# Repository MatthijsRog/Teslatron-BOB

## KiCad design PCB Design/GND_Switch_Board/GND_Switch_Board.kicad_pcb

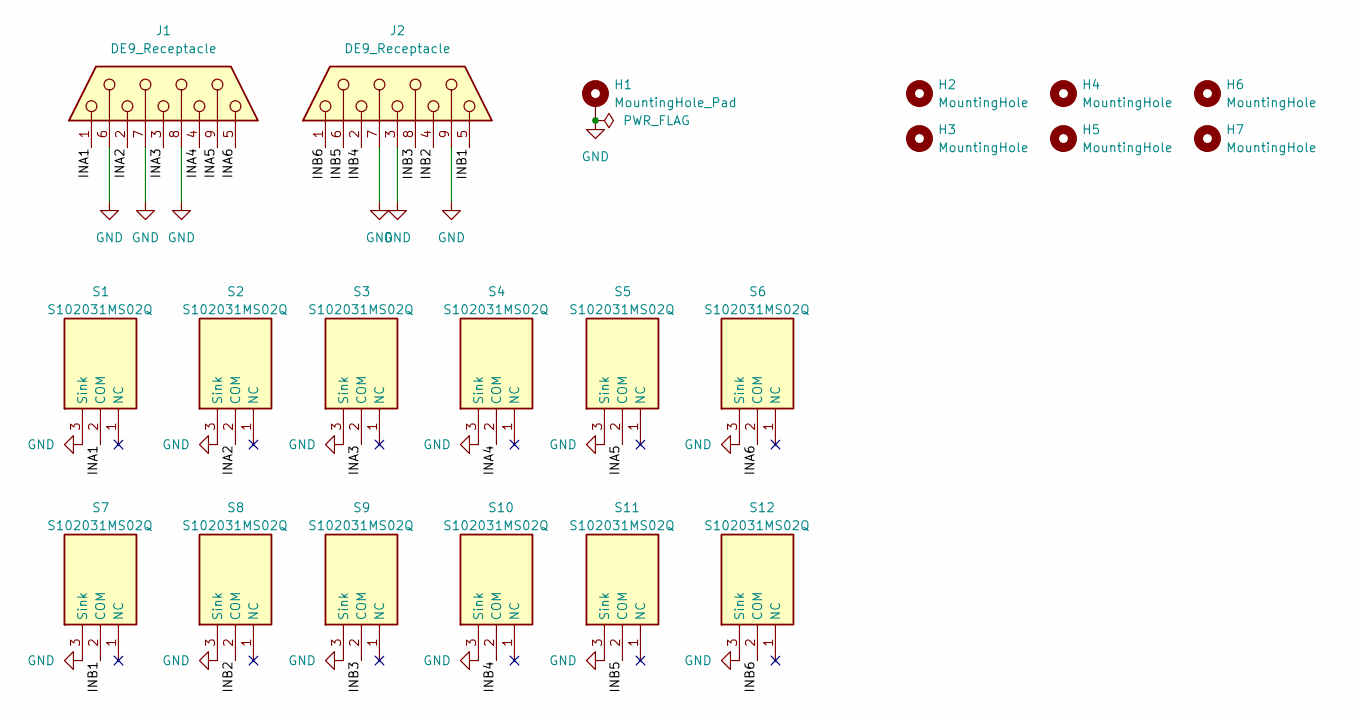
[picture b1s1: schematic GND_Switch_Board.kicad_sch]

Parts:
H1: MountingHole_Pad; MountingHole_3.2mm_M3_DIN965_Pad_TopBottom
H2, H3, H4, H5, H6, H7: MountingHole; MountingHole_3.2mm_M3_DIN965
J1, J2: DE9_Receptacle; 43383132
S1, S2, S3, S4, S5, S6, S7, S8, S9, S10, S11, S12: S102031MS02Q; Mouser Part Number 611-S1020301

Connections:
/INA1: J1.1, S1.2 (COM)
/INA2: J1.2, S2.2 (COM)
/INA3: J1.3, S3.2 (COM)
/INA4: J1.4, S4.2 (COM)
/INA5: J1.9, S5.2 (COM)
/INA6: J1.5, S6.2 (COM)
/INB1: J2.5, S7.2 (COM)
/INB2: J2.4, S8.2 (COM)
/INB3: J2.8, S9.2 (COM)
/INB4: J2.2, S10.2 (COM)
/INB5: J2.6, S11.2 (COM)
/INB6: J2.1, S12.2 (COM)
GND: H1.1, J1.6, J1.7, J1.8, J2.3, J2.7, J2.9, S1.3 (Sink), S2.3 (Sink), S3.3 (Sink), S4.3 (Sink), S5.3 (Sink), S6.3 (Sink), S7.3 (Sink), S8.3 (Sink), S9.3 (Sink), S10.3 (Sink), S11.3 (Sink), S12.3 (Sink)

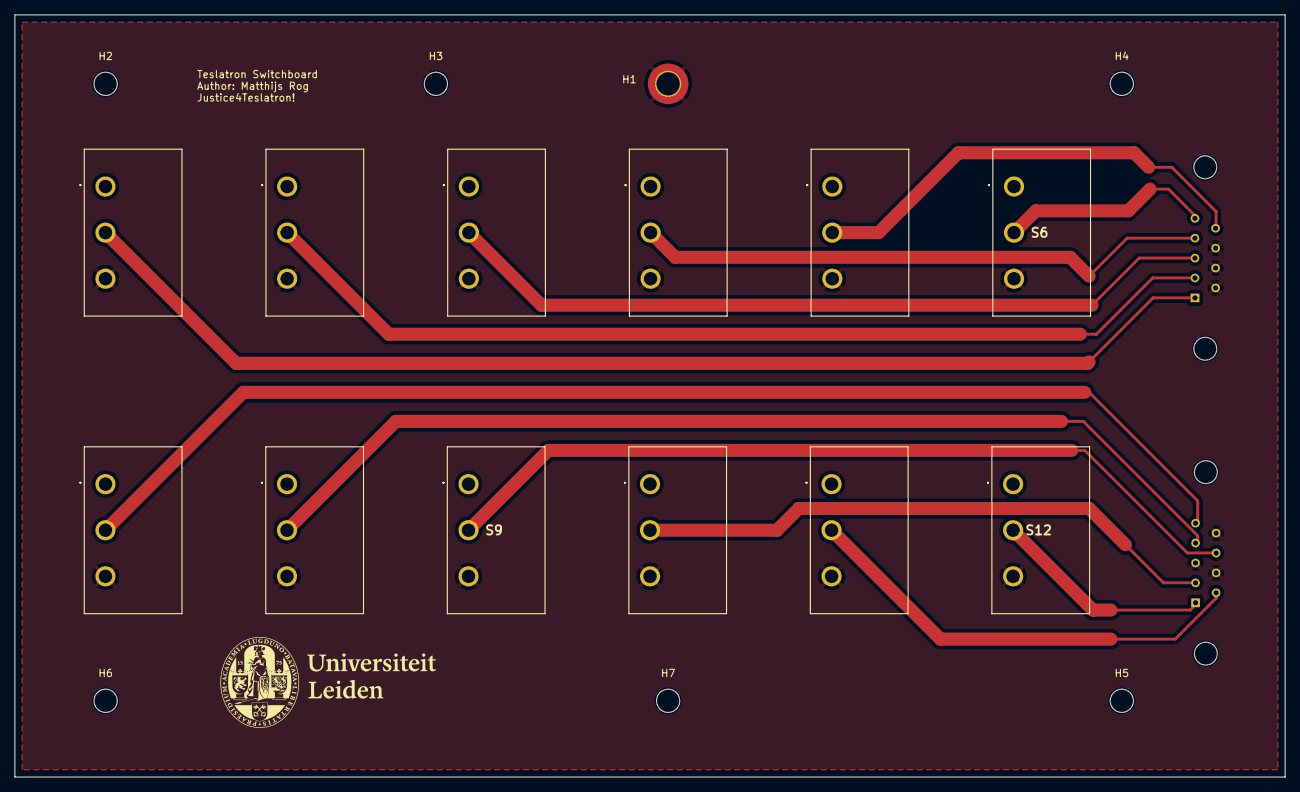
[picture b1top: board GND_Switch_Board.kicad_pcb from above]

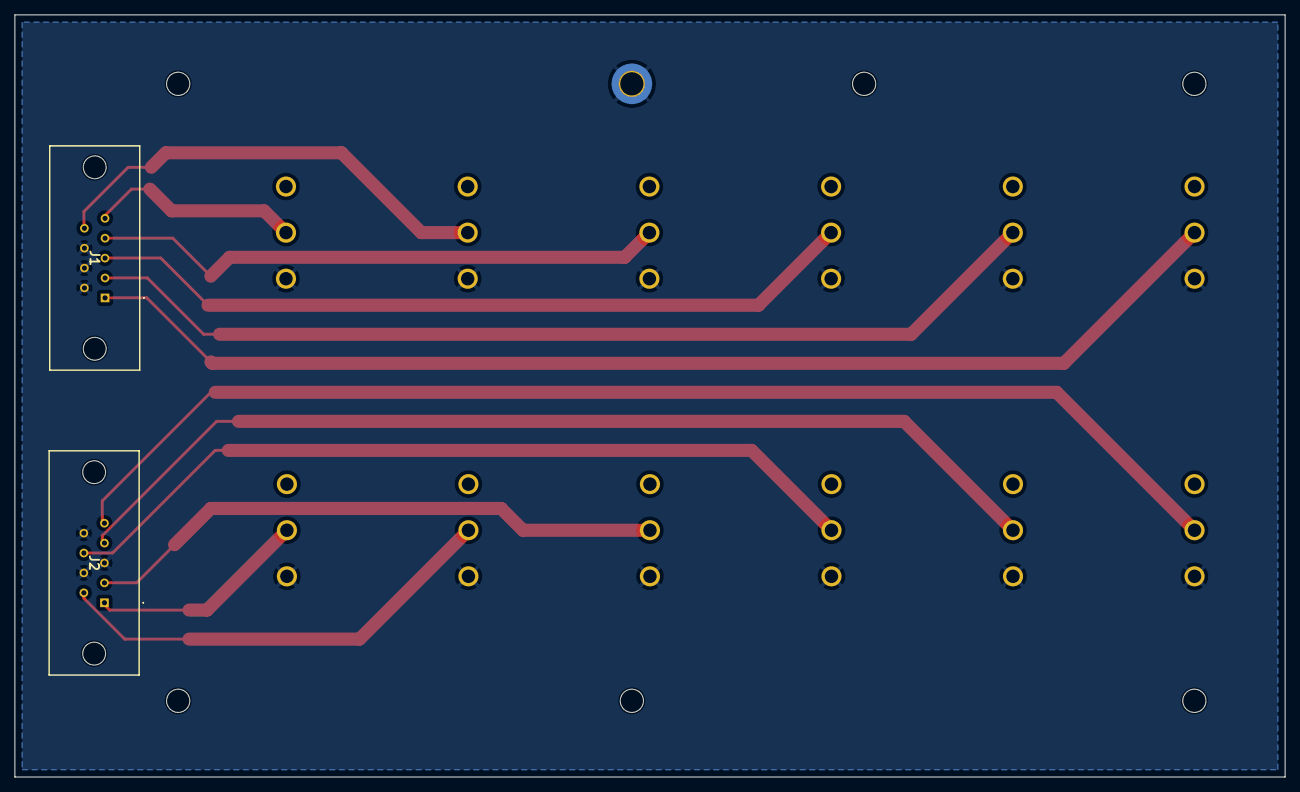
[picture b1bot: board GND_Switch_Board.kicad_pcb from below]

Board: 2 copper layers, 175.0 x 105.0 mm, 21 parts (2 on the bottom side), 13 nets.

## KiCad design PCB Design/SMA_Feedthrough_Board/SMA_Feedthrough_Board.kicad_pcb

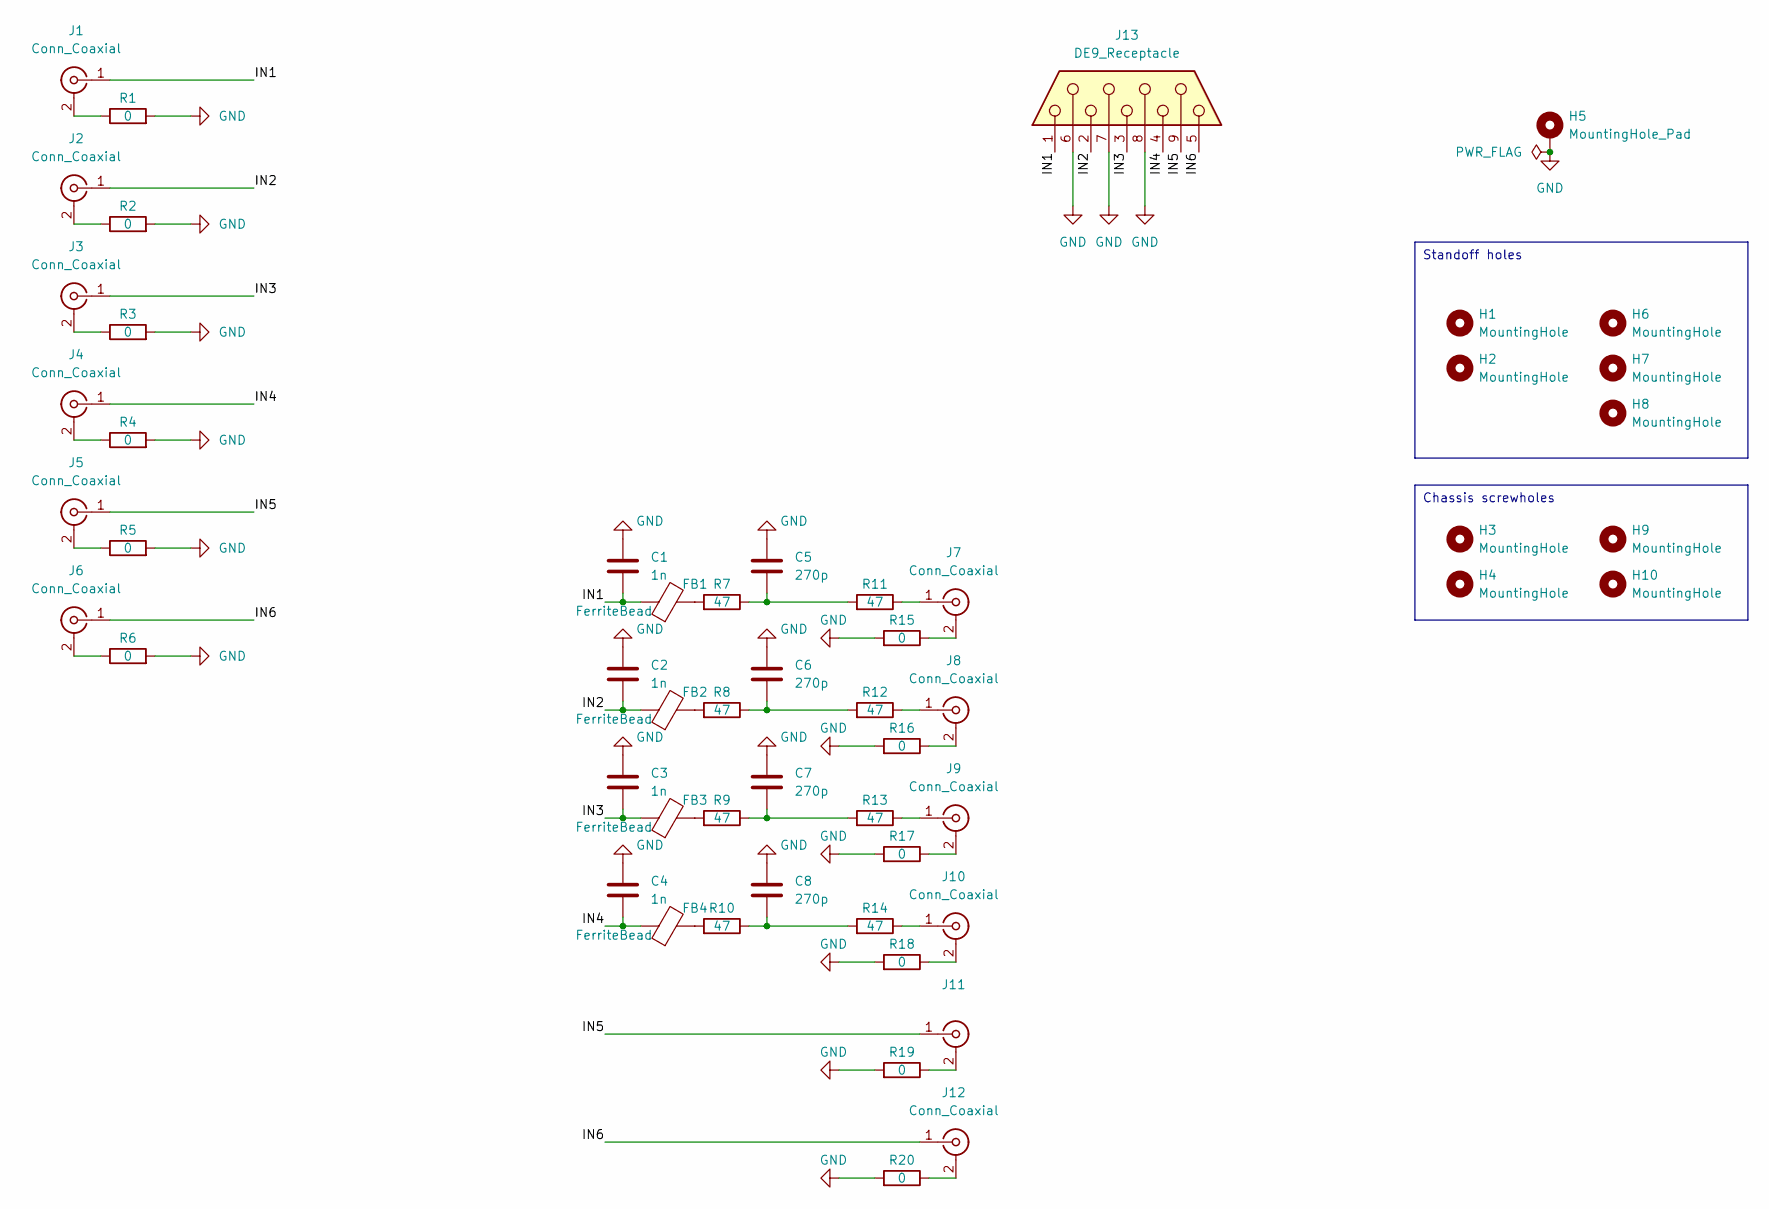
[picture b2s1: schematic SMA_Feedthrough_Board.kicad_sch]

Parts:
C1, C2, C3, C4: 1n; C_0805_2012Metric_Pad1.18x1.45mm_HandSolder
C5, C6, C7, C8: 270p; C_0805_2012Metric_Pad1.18x1.45mm_HandSolder
FB1, FB2, FB3, FB4: FerriteBead; R_0603_1608Metric_Pad0.98x0.95mm_HandSolder
H1, H2, H3, H4, H6, H7, H8, H9, H10: MountingHole; MountingHole_3.2mm_M3_DIN965
H5: MountingHole_Pad; MountingHole_3.2mm_M3_DIN965_Pad
J1, J2, J3, J4, J5, J6, J7, J8, J9, J10, J11, J12: Conn_Coaxial; AMPHENOL_901-143-6RFX
J13: DE9_Receptacle; 1-5393480-5
R1, R2, R3, R4, R5, R6, R15, R16, R17, R18, R19, R20: 0; R_1206_3216Metric_Pad1.30x1.75mm_HandSolder
R7, R8, R9, R10, R11, R12, R13, R14: 47; R_1206_3216Metric_Pad1.30x1.75mm_HandSolder

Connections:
/IN1: C1.2, FB1.1, J1.1 (In), J13.1
/IN2: C2.2, FB2.1, J2.1 (In), J13.2
/IN3: C3.2, FB3.1, J3.1 (In), J13.3
/IN4: C4.2, FB4.1, J4.1 (In), J13.4
/IN5: J5.1 (In), J11.1 (In), J13.9
/IN6: J6.1 (In), J12.1 (In), J13.5
GND: C1.1, C2.1, C3.1, C4.1, C5.1, C6.1, C7.1, C8.1, H5.1, J13.6, J13.7, J13.8, R1.2, R2.2, R3.2, R4.2, R5.2, R6.2, R15.2, R16.2, R17.2, R18.2, R19.2, R20.2
unnamed: C5.2, R7.1, R11.2
unnamed: C6.2, R8.1, R12.2
unnamed: C7.2, R9.1, R13.2
unnamed: C8.2, R10.1, R14.2
unnamed: FB1.2, R7.2
unnamed: FB2.2, R8.2
unnamed: FB3.2, R9.2
unnamed: FB4.2, R10.2
unnamed: J1.2 (Ext), R1.1
unnamed: J2.2 (Ext), R2.1
unnamed: J3.2 (Ext), R3.1
unnamed: J4.2 (Ext), R4.1
unnamed: J5.2 (Ext), R5.1
unnamed: J6.2 (Ext), R6.1
unnamed: J7.2 (Ext), R15.1
unnamed: J7.1 (In), R11.1
unnamed: J8.2 (Ext), R16.1
unnamed: J8.1 (In), R12.1
unnamed: J9.2 (Ext), R17.1
unnamed: J9.1 (In), R13.1
unnamed: J10.2 (Ext), R18.1
unnamed: J10.1 (In), R14.1
unnamed: J11.2 (Ext), R19.1
unnamed: J12.2 (Ext), R20.1

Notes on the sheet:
Standoff holes
Chassis screwholes

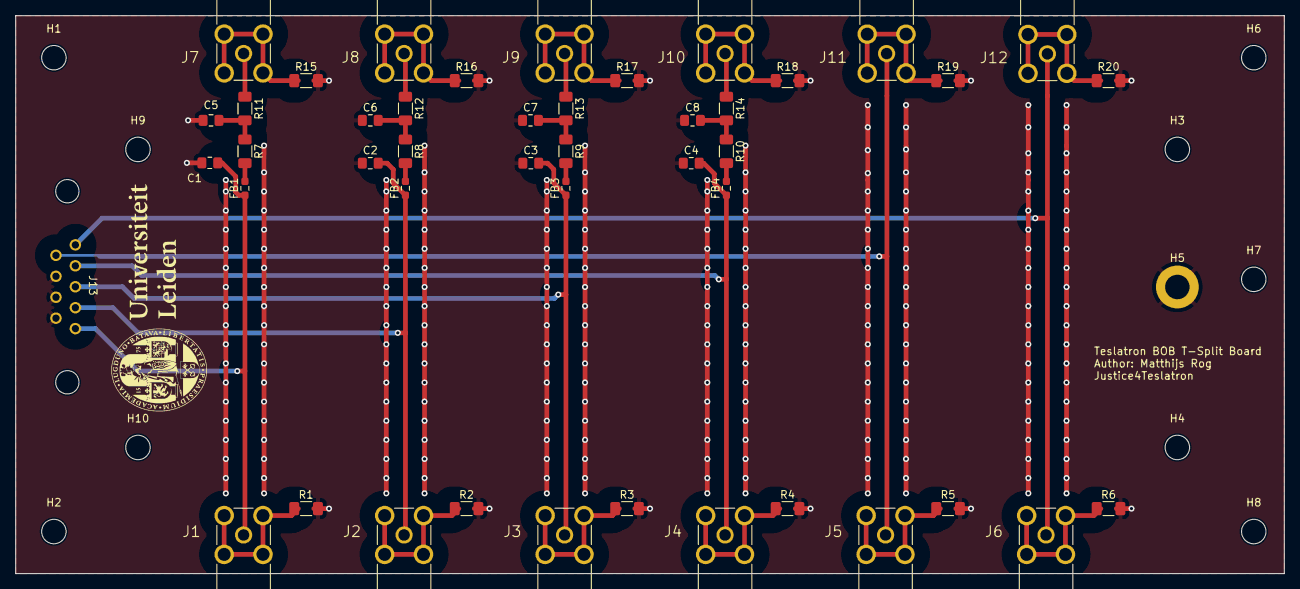
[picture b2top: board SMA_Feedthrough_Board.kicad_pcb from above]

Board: 4 copper layers, 166.0 x 73.0 mm, 55 parts (0 on the bottom side), 31 nets.

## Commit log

2024-04-11 Revision 1
2024-04-11 Create LICENSE
